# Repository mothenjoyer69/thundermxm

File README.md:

# thundermxm
An open source MXM eGPU board featuring an Intel JHL7440 TB3 controller module, with support for 200W of power. It supports standard MXM3.0A/B cards, as well as Clevo style cards, and supports both TB3 display tunneling and native display output. 

* Very WIP Kicad render

# Specs:
* Intel JHL7440 TB3 module 
* MXM3.0b interface, with full support for Clevo power connectors
* PCIe 3.0 x4 link
* All available I/O broken out:
    * 3x DP + 1x HDMI for monitor and VR headset support
    * USB3.0 downstream ports for various devices
* Dell-style 15A barrel jack connector
* Fan header with PWM control (Planned)

## To-do:
* Finalize schematics, now that reference files for the TB3 module have arrived
* Finish routing (waiting on schematic)

This project wouldn't exist without the help of [wifi](https://github.com/a-little-wifi/) and her incredible [MXM Immobilizer project](https://github.com/a-little-wifi/mxm-immobilizer). I also stole the cool MXM outline from there :3

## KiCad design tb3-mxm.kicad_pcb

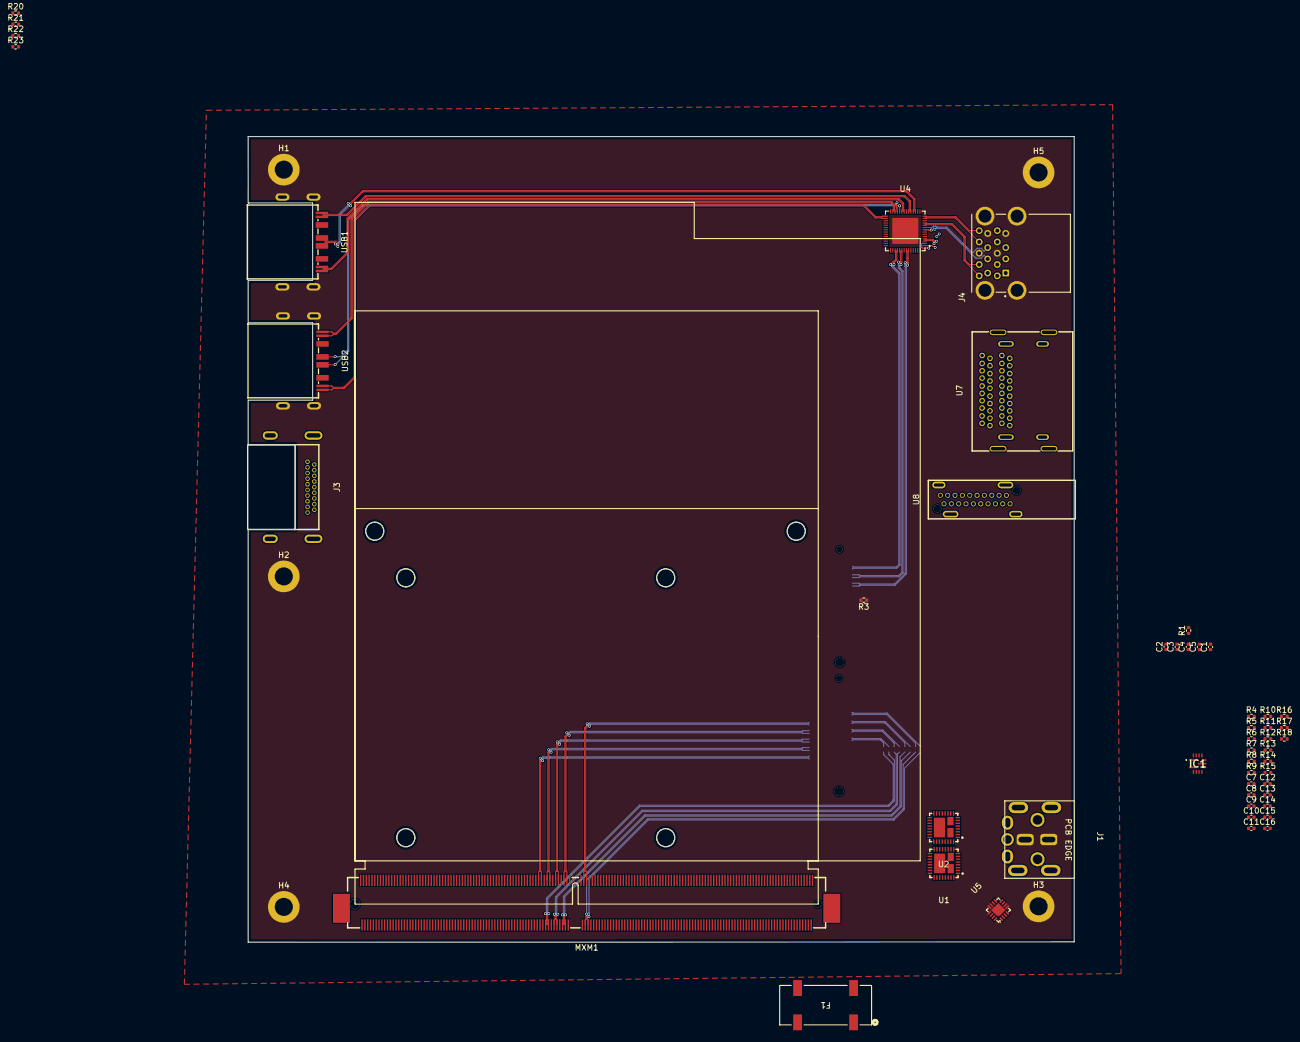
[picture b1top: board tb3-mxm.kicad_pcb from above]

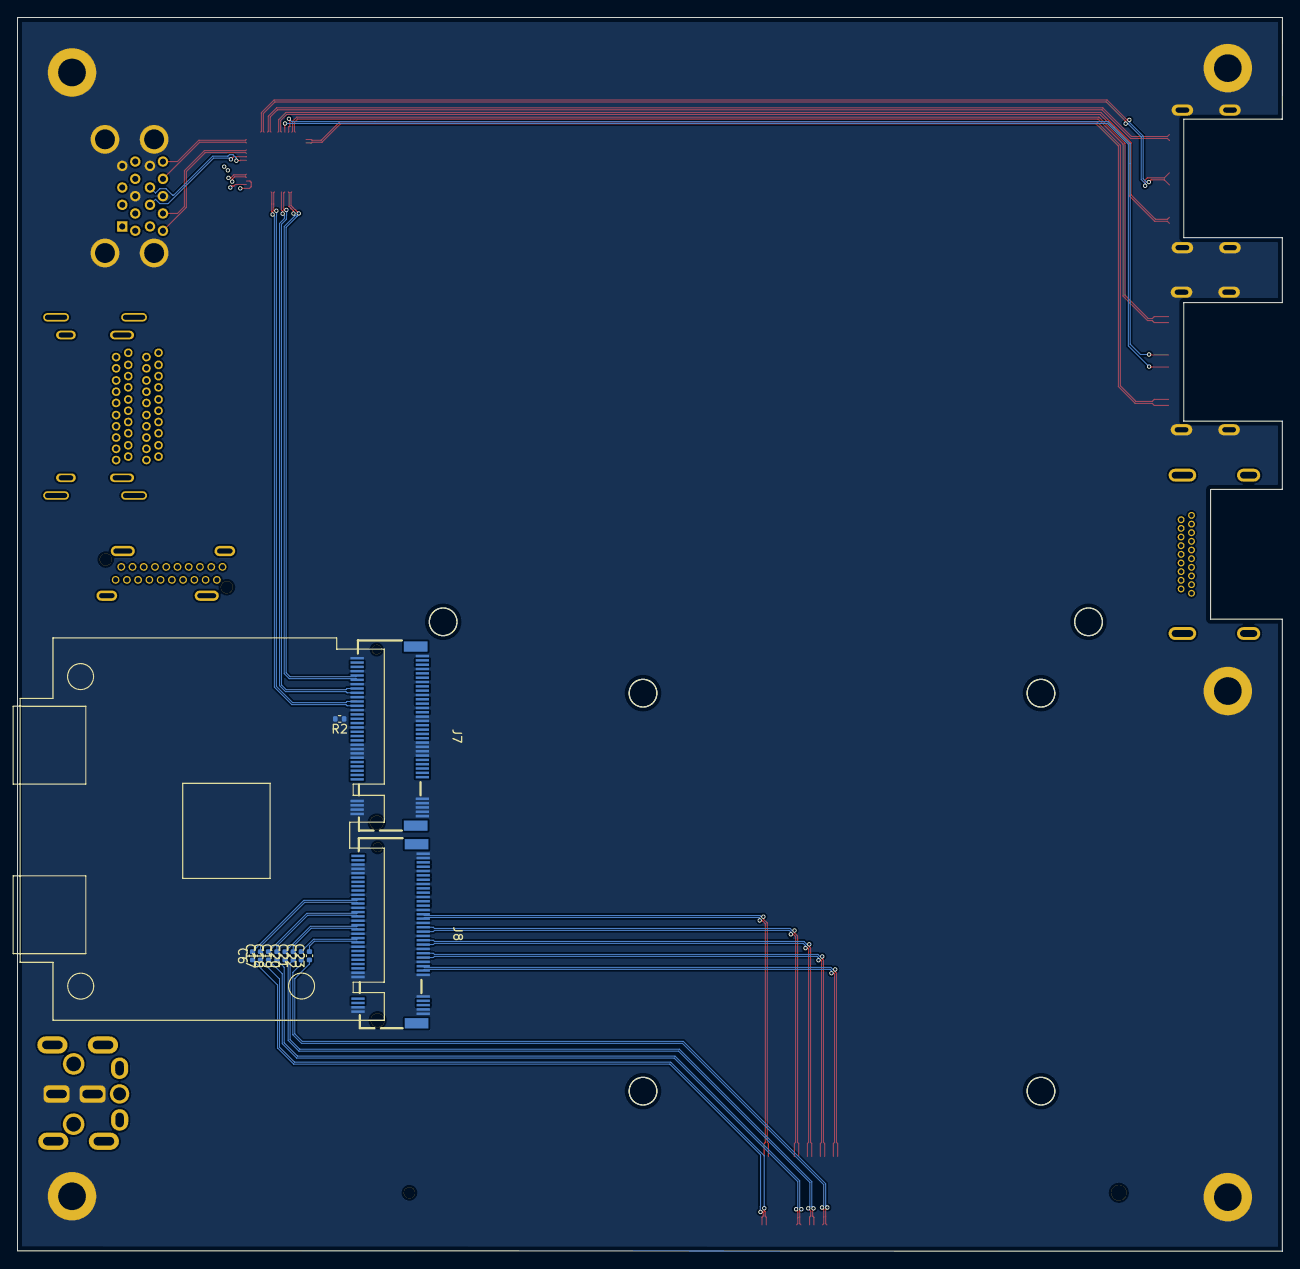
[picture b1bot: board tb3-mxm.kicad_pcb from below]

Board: 4 copper layers, 146.2 x 142.6 mm, 66 parts (11 on the bottom side), 86 nets.

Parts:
C1, C3: 10uF/16v; C_0402_1005Metric
C2, C4, C5: 1uF/16v; C_0402_1005Metric
C6, C17, C18, C19, C20, C21, C22, C23: 100n; C_0402_1005Metric
C7: 22uF/25V; C_0402_1005Metric
C8: 22uF/25v; C_0402_1005Metric
C9: 10n/25v; C_0402_1005Metric
C10: 2.2uF/25v; C_0402_1005Metric
C11: 1u/50v; C_0402_1005Metric
C12, C15: 22uF/35v; C_0402_1005Metric
C13, C14: 220uF/16V; C_0402_1005Metric
C16: 18p/25v; C_0402_1005Metric
F1: Fuse; 3588_KEY
H1, H2, H3, H4, H5: MountingHole_Pad; MountingHole_3.2mm_M3_DIN965_Pad
IC1: MP2491CGQB-P; MP2491CGQBP
J1: Jack-DC; DC-505
J3: HDMI_FRONT; HDMI-SMD_U-C-19DD-W-1
J4: USB3_DOUBLE; MOLEX_0484060003
J7: M.2_1_USB; PCI-SMD_APCI0079-P002A
J8: M.2_2_PCIE; PCI-SMD_APCI0079-P002A
MXM1: AS0B826-S78B-7H; CONN-SMD_AS0B826-S78B-7H
R1, R3: 0k; R_0402_1005Metric
R2: 0k (NC); R_0402_1005Metric
R4, R10, R11, R14: 100k; R_0402_1005Metric
R5: 200k; R_0402_1005Metric
R6, R7, R8: 10k; R_0402_1005Metric
R9, R12, R13, R16, R17, R18: 0; R_0402_1005Metric
R15: 11k; R_0402_1005Metric
R20, R22, R23: R_Small; R_0402_1005Metric
R21: 80k; R_0402_1005Metric
U1: 5V-DCDC; MLP55-32_L5.0-W5.0-P0.50-TL-EP
U2: 3v3-DCDC; MLP55-32_L5.0-W5.0-P0.50-TL-EP
U4: USB5744T/2GX01; VQFN-56_L7.0-W7.0-P0.40-BR-EP4.6
U5: TPS55340RTER; VQFN-16_L3.0-W3.0-P0.50-BL-EP1.7
U7: DISPLAYPORT_DOUBLE; DP-TH_3VD11203-DPA1-4H
U8: DP_REAR; USB-TH_3VD21203-H7U0-4H
USB1: USB2_FRONT1; USB-A-SMD_HC-USB3.0-C345-P
USB2: USB2_FRONT2; USB-A-SMD_HC-USB3.0-C345-P

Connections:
+1V2: U4.5 (VDD12), U4.12 (VDD12), U4.15 (VDD12), U4.21 (VDD12), U4.28 (VDD12), U4.33 (VDD12), U4.43 (VDD12), U4.49 (VDD12)
+3V3: U4.16 (VDD33), U4.31 (VDD33), U4.37 (VBUS_DET), U4.44 (VDD33), U4.55 (VDD33)
+5V: J4.1 (VBUS_U1), J4.10 (VBUS_U2), USB1.1 (VBUS), USB1.4 (GND), USB2.1 (VBUS), USB2.4 (GND)
/MXM/PCIE_TX0_C_N: C22.1, MXM1.148 (PEX_TX0#)
/MXM/PCIE_TX0_C_P: C23.1, MXM1.150 (PEX_TX0)
/MXM/PCIE_TX1_C_N: C20.1, MXM1.142 (PEX_TX1#)
/MXM/PCIE_TX1_C_P: C21.1, MXM1.144 (PEX_TX1)
/MXM/PCIE_TX2_C_N: C18.1, MXM1.136 (PEX_TX2#)
/MXM/PCIE_TX2_C_P: C19.1, MXM1.138 (PEX_TX2)
/MXM/PCIE_TX3_C_N: C6.1, MXM1.120 (PEX_TX3#)
/MXM/PCIE_TX3_C_P: C17.1, MXM1.122 (PEX_TX3)
/POWER/AN_VCCHV_BST: IC1.9 (BST), R13.1
/POWER/AN_VCCHV_BST_R: C11.2, R13.2
/POWER/AN_VCCHV_FB: C16.2, IC1.6 (FB), R14.1, R15.2
/POWER/AN_VCCHV_ILIM: IC1.12 (ILIM), R10.2, R11.2
/POWER/DG_PDO_VSEL1_1: IC1.4 (VSEL1), R7.2, R17.1
/POWER/DG_PDO_VSEL2_2: IC1.5 (VSEL2), R8.2, R18.1
/POWER/DG_VCCHV_EN: C9.2, IC1.11 (EN), R4.2, R5.2, R16.1
/POWER/DG_VCCHV_MODE: IC1.10 (MODE), R9.2, R12.2
/POWER/DG_VCCHV_PG: IC1.13 (PG), R6.2
/POWER/PW_VCCHW_SW: C11.1, IC1.8 (SW)
/POWER/PW_VCHH_VCC: C10.1, IC1.3 (VCC), R6.1, R7.1, R8.1, R9.1
GND: C1.2, C2.2, C3.2, C4.2, C5.2, C7.1, C8.1, C9.1, C10.2, C12.2, C13.2, C14.2, C15.2, H1.1, H2.1, H3.1, H4.1, H5.1, IC1.2 (PGND), IC1.7 (AGND), J1.1 (GND), J4.4 (GND_U1), J4.7 (GND_DRAIN_U1), J4.13 (GND_U2), J4.16 (GND_DRAIN_U2), J4.S1 (SHIELD), J4.S2 (SHIELD__1), J4.S3 (SHIELD__2), J4.S4 (SHIELD__3), J7.1, J7.2, J7.7, J7.8, J7.13, J7.14, J7.19, J7.20, J7.25, J7.26, J7.29, J7.31, J7.34, J7.41, J7.42, J7.43, J7.44, J7.45, J7.46, J7.47, J7.48, J7.67, J7.68, J7.69, J7.70, J7.71, J7.72, J7.73, J7.74, J7.75, J8.1, J8.3, J8.6, J8.8, J8.9, J8.10, J8.15, J8.20, J8.21, J8.26, J8.27, J8.32, J8.33, J8.38, J8.39, J8.44, J8.45, J8.51, J8.56, J8.57, J8.58, J8.67, J8.72, J8.73, J8.74, J8.75, R4.1, R10.1, R11.1, R12.1, R15.1, R21.2, R22.2, U4.52 (ATEST), U4.57 (VSS), U5.5 (SYNC), U5.6 (AGND), U5.11 (PGND), U5.12 (PGND), U5.13 (PGND), U5.17 (EP), USB1.10 (GND), USB1.11 (GND), USB1.12 (GND), USB1.13 (GND), USB2.10 (GND), USB2.11 (GND), USB2.12 (GND), USB2.13 (GND)
MXM_VCC_20V: F1.3, MXM1.E1 (E1_PWR_SRC), MXM1.E2 (E2_PWR_SRC)
unnamed: U5.1 (SW), U5.15 (SW), U5.16 (SW)
unnamed: J7.28, R1.1
unnamed: J7.30, R2.1
unnamed: J7.32, R3.1
unnamed: MXM1.1 (5V), MXM1.3 (5V), MXM1.5 (5V), MXM1.7 (5V), MXM1.9 (5V)
unnamed: R20.1, U5.7 (COMP)
unnamed: R22.1, R23.2, U5.8 (FB)
unnamed: R21.1, U5.9 (FREQ)
PCIE_CLK100M_N: J8.53, MXM1.155 (PEX_REFCLK)
PCIE_CLK100M_P: J8.55, MXM1.153 (PEX_REFCLK#)
PCIE_RX0_N: J8.47, MXM1.149 (PEX_RX0)
PCIE_RX0_P: J8.49, MXM1.147 (PEX_RX0#)
PCIE_RX1_N: J8.41, MXM1.143 (PEX_RX1)
PCIE_RX1_P: J8.43, MXM1.141 (PEX_RX1#)
PCIE_RX2_N: J8.35, MXM1.137 (PEX_RX2)
PCIE_RX2_P: J8.37, MXM1.135 (PEX_RX2#)
PCIE_RX3_N: J8.29, MXM1.123 (PEX_RX3)
PCIE_RX3_P: J8.31, MXM1.121 (PEX_RX3#)
PCIE_TX0_N: C22.2, J8.40
PCIE_TX0_P: C23.2, J8.42
PCIE_TX1_N: C20.2, J8.34
PCIE_TX1_P: C21.2, J8.36
PCIE_TX2_N: C18.2, J8.28
PCIE_TX2_P: C19.2, J8.30
PCIE_TX3_N: C6.2, J8.22
PCIE_TX3_P: C17.2, J8.24
PW_VCC3v3: C3.1, C4.1, C5.1, J8.68, J8.69, J8.70, J8.71
PW_VCC5v0_SYS: C1.1, C2.1, J8.2, J8.4
PW_VCC_TBTA_VBUS: C12.1, C13.1, C14.1, C15.1, C16.1, J7.49, J7.50, J7.51, J7.52, J7.53, J7.54, J7.55, J7.56, J7.57, J7.58, R14.2
PW_VCC_TBTB_VBUS: J7.33, J7.35, J7.36, J7.37, J7.38, J7.39, J7.40
USB0_D_N: J7.12, U4.46 (USB2UP_DM)
USB0_D_P: J7.10, U4.45 (USB2UP_DP)
USB0_SSRX1_N: J7.24, U4.51 (USB3UP_RXDM)
USB0_SSRX1_P: J7.22, U4.50 (USB3UP_RXDP)
USB0_SSTX1_N: J7.18, U4.48 (USB3UP_TXDM)
USB0_SSTX1_P: J7.16, U4.47 (USB3UP_TXDP)
USB1_D_N: J4.2 (D-_U1), U4.2 (USB2DN_DM1/~PRT_DIS_M1)
USB1_D_P: J4.3 (D+_U1), U4.1 (USB2DN_DP1/~PRT_DIS_P1)
USB1_SSRX_N: J4.5 (STDA_SSRX-_U1), U4.6 (USB3DN_RXDP1)
USB1_SSRX_P: J4.6 (STDA_SSRX+_U1), U4.7 (USB3DN_RXDM1)
USB1_SSTX_N: J4.8 (STDA_SSTX-_U1), U4.4 (USB3DN_TXDM1)
USB1_SSTX_P: J4.9 (STDA_SSTX+_U1), U4.3 (USB3DN_TXDP1)
USB2_D_N: J4.11 (D-_U2), U4.9 (USB2DN_DM2/~PRT_DIS_M2)
USB2_D_P: J4.12 (D+_U2), U4.8 (USB2DN_DP2/~PRT_DIS_P2)
USB2_SSRX_N: J4.14 (STDA_SSRX-_U2), U4.14 (USB3DN_RXDM2)
USB2_SSRX_P: J4.15 (STDA_SSRX+_U2), U4.13 (USB3DN_RXDP2)
USB2_SSTX_N: J4.17 (STDA_SSTX-_U2), U4.11 (USB3DN_TXDM2)
USB2_SSTX_P: J4.18 (STDA_SSTX+_U2), U4.10 (USB3DN_TXDP2)
USB3_D_N: U4.18 (USB2DN_DM3/~PRT_DIS_M3), USB1.2 (D-)
USB3_D_P: U4.17 (USB2DN_DP3/~PRT_DIS_P3), USB1.3 (D+)
USB3_SSRX_N: U4.23 (USB3DN_RXDM3), USB1.5 (STDA_SSRX-)
USB3_SSRX_P: U4.22 (USB3DN_RXDP3), USB1.6 (STDA_SSRX+)
USB3_SSTX_N: U4.20 (USB3DN_TXDM3), USB1.8 (STDA_SSTX-)
USB3_SSTX_P: U4.19 (USB3DN_TXDP3), USB1.9 (STDA_SSTX+)
USB4_D_N: U4.25 (USB2DN_DM4/~PRT_DIS_M4), USB2.2 (D-)
USB4_D_P: U4.24 (USB2DN_DP4/~PRT_DIS_P4), USB2.3 (D+)
USB4_SSRX_N: U4.30 (USB3DN_RXDM4), USB2.5 (STDA_SSRX-)
USB4_SSRX_P: U4.29 (USB3DN_RXDP4), USB2.6 (STDA_SSRX+)
USB4_SSTX_N: U4.27 (USB3DN_TXDM4), USB2.8 (STDA_SSTX-)
USB4_SSTX_P: U4.26 (USB3DN_TXDP4), USB2.9 (STDA_SSTX+)
VCC_22V: C7.2, C8.2, IC1.1 (IN), R5.1, R23.1
VIN_20V: F1.1, J1.2 (V+), U5.2 (VIN), U5.3 (EN)

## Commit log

2025-06-02 add initial files
2025-06-02 gitignore
